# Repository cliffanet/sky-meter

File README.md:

# Высотомер Sky-Meter

Инструмент для парашютиста - простой высотомер на базе барометра.

***
## Что умеет

* измерять высоту;
* определять начала подъёма и начало прыжка;
* писать в логбук историю прыжков: время взлёта, высота отделения, высота раскрытия;

***
## Внутри

***
## Документация

* [Исходники](doc/code.md) - где, что лежит, права на использование, помощь при компиляции.
* [Где скачать](doc/download.md)

***
## Известные проблемы

- повышенное энергопотребление в спящем режиме (850 мкА)

    В первой аппаратной версии применялся чип stm32f473 и энергопотребление всего устройства
    на его основе удалось снизить до 125 мкА, а в выключенном - до 85-90 мкА. И это
    при заявленных в документации 56 мкА (что-то дополнительно подребляет и сама плата).

    А вот на чипе stm32f411 при заявленных в документации 10 мкА получить потребление ниже
    60 мкА так и не удалось - но это на пустой прошивке. На боевой же прошивке почему-то
    не отключаются какие-то узлы, и потребление ~850 мкА. С этим ещё предстоит разобраться.

- нестабильная работа с SD-картой

    Проблема возникает из-за слабого питания, подаваемого на карту. В целях экономии заряда
    батареи питание на SD-карту выведено напрямую с пина микроконтроллера. Применение дополнительного
    транзистора в режиме ключа вызывает проблемы из-за низкого потребляемого тока карты (несколько мА).
    При инициализации карты ток возрастает и питание проседает, из-за чего карта сбрасывается.

    Некоторые карты всё же работают, но таких мало.

    На stm32g4xx работа карт от пина была гораздо стабильнее. Но всё же, на некоторых картах тоже
    были сбои.

    В качестве оперативной меры можно перерезать дорожку, ведущую к пину МК и соединить питание карты
    напрямую на 3.3v. Однако потребление в спящем режиме вместе с SD-картой возрастает до 3 мА.

- отсутствие приложения для импорта логбука

    Разработка отложена на неопределённый срок.

***

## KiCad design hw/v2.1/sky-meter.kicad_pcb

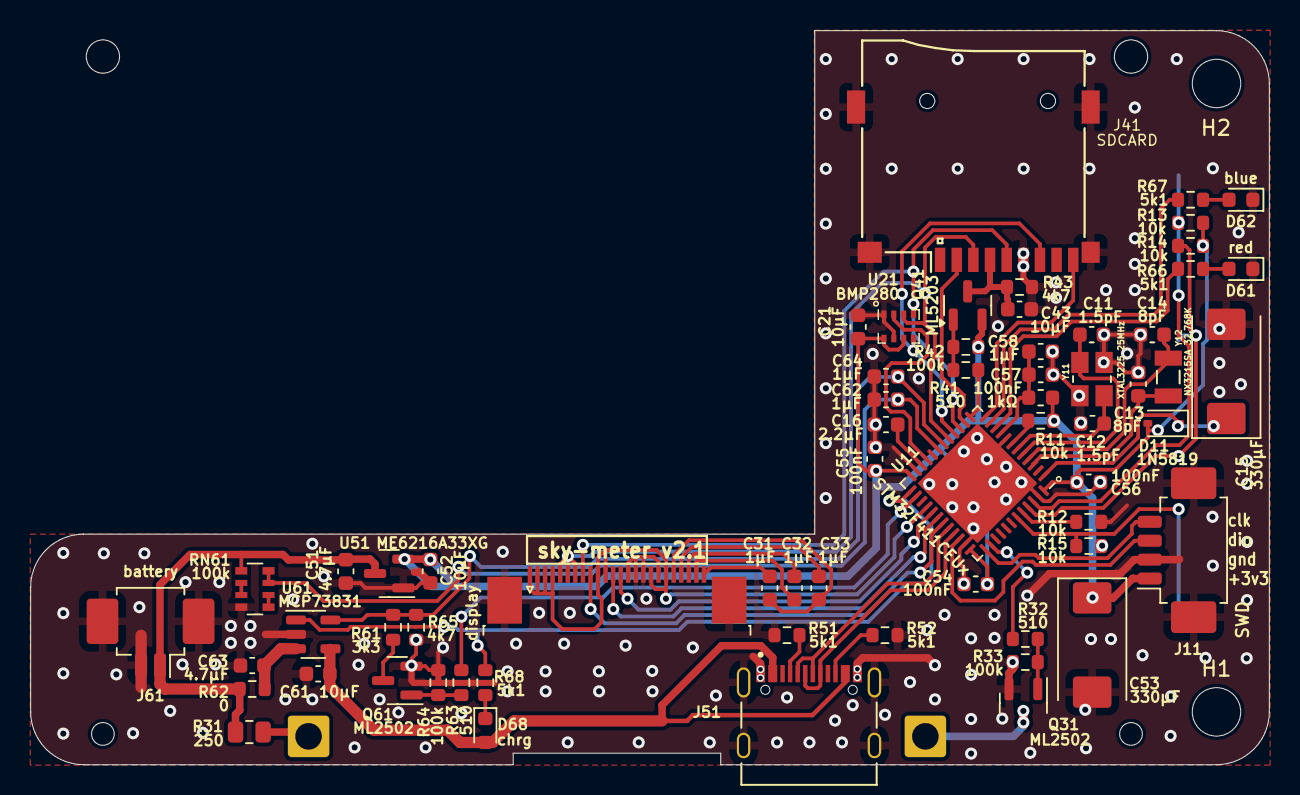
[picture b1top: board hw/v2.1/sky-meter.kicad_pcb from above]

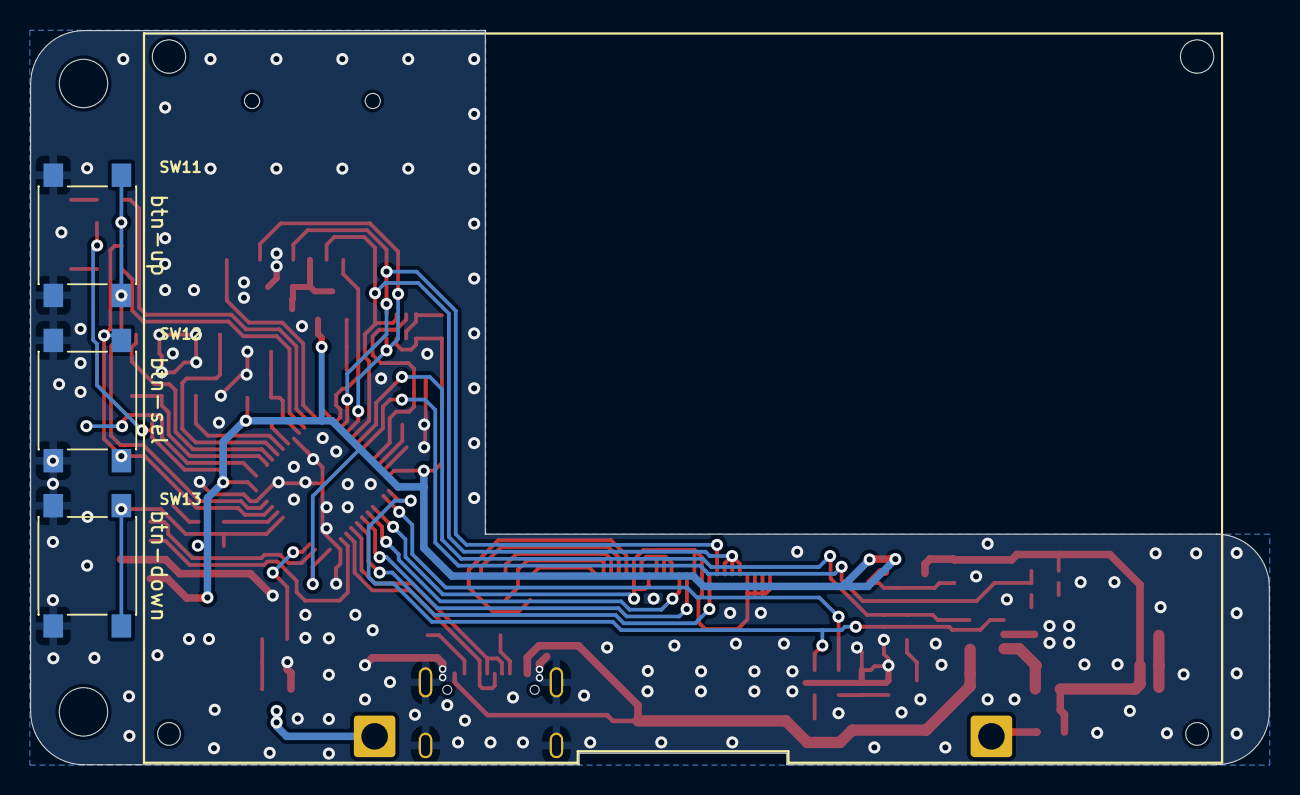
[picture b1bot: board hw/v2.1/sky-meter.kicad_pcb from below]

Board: 2 copper layers, 81.9 x 48.5 mm, 70 parts (3 on the bottom side), 58 nets.

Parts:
C11, C12: 1.5pF; C_0603_1608Metric
C13, C14: 8pF; C_0603_1608Metric
C15, C53: 330μF; CP_EIA-7343-20_Kemet-V
C16: 2.2μF; C_0603_1608Metric
C21, C43, C52, C61: 10μF; C_0603_1608Metric
C31, C32, C33, C58, C62, C64: 1μF; C_0603_1608Metric
C51, C63: 4.7μF; C_0603_1608Metric
C54, C55, C56, C57: 100nF; C_0603_1608Metric
D11: 1N5819; D_SOD-323
D61: red; LED_0603_1608Metric
D62: blue; LED_0603_1608Metric
D68: chrg; LED_0603_1608Metric
FB51: 1kΩ; L_0603_1608Metric
H1, H2: MountingHole; MountingHole_3.2mm_M3
J11: SWD; Molex_PicoBlade_53261-0471_1x04-1MP_P1.25mm_Horizontal
J31: display; TE_2-1734839-4_1x24-1MP_P0.5mm_Horizontal
J32: display-128x64
J41: SDCARD; Conn_uSDcard
J51: TYPE-C-31-M-12; HRO_TYPE-C-31-M-12
J61: battery; Molex_PicoBlade_53261-0271_1x02-1MP_P1.25mm_Horizontal
Q31, Q61: ML2502; SOT-23
Q41: ML5203; SOT-23
R11, R12, R13, R14, R15: 10k; R_0603_1608Metric
R31: 250; R_0805_2012Metric
R32, R41, R63: 510; R_0603_1608Metric
R33, R42, R64: 100k; R_0603_1608Metric
R43, R65: 4k7; R_0603_1608Metric
R51, R52, R66, R67, R68: 5k1; R_0603_1608Metric
R61: 3k3; R_0603_1608Metric
R62: 0; R_0603_1608Metric
RN61: 100k; R_Array_Convex_4x0603
SW11: btn-up; SW_Push_1P1T_NO_6x6mm_H9.5mm
SW12: btn-sel; SW_Push_1P1T_NO_6x6mm_H9.5mm
SW13: btn-down; SW_Push_1P1T_NO_6x6mm_H9.5mm
U11: STM32F411CEUx; QFN-48-1EP_7x7mm_P0.5mm_EP5.6x5.6mm
U21: BMP280; Bosch_LGA-8_2x2.5mm_P0.65mm_ClockwisePinNumbering
U51: ME6216A33XG; SOT-23
U61: MCP73831; SOT-23-5
Y11: XTAL3225 25MHz; XTAL_TSX-3225_16.0000MF18X-AC3
Y12: NX3215SA 32.768K; XTAL_NX3215SA-32.768K-STD-MUA-14

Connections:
+3.3VA: C57.2, C58.2, FB51.2, U11.9 (VDDA)
+3V3: C21.1, C52.2, C53.1, C54.1, C55.1, C56.1, D11.2 (A), FB51.1, J11.1, Q41.2 (S), R11.1, R13.1, R14.1, R15.1, R42.2, U11.24 (VDD), U11.36 (VDD), U11.48 (VDD), U21.6 (VDDIO), U21.8 (VDD), U51.2 (VO)
+BATT: C51.1, J61.1, R31.2, R62.2, RN61.1 (R1.1), U51.3 (VI)
/btn-dn: R15.2, SW13.2 (B), U11.43 (PB7)
/btn-sel: R14.2, SW12.2 (B), U11.45 (PB8)
/btn-up: R13.2, SW11.2 (B), U11.46 (PB9)
/d-cs: J31.13, U11.29 (PA8)
/d-en: J31.1, J31.2, J31.3, J31.4, J31.10, J31.11, J31.17, J31.19, U11.28 (PB15)
/d-rs-dc: J31.12, U11.30 (PA9)
/d-rst: J31.9, U11.31 (PA10)
/led-b: R67.2, U11.11 (PA1)
/led-r: R66.2, U11.10 (PA0)
/sdcard-cd: J41.9 (CD), U11.12 (PA2)
/sdcard-cs: J41.2 (CS/DAT3), U11.14 (PA4)
/sdcard-en: R41.2, U11.13 (PA3)
/spi-clk: J31.8, J41.5 (CLK), U11.15 (PA5), U21.4 (SCK)
/spi-miso: J41.7 (DO/DAT0), U11.16 (PA6), U21.5 (SDO)
/spi-mosi: J31.5, J31.6, J31.7, J41.3 (DI/CMD), U11.17 (PA7), U21.3 (SDI)
/swclk: J11.4, U11.37 (PA14)
/swdio: J11.3, U11.34 (PA13)
/usb-d+: J51.A6 (DP1), J51.B6 (DP2), U11.33 (PA12)
/usb-d-: J51.A7 (DN1), J51.B7 (DN2), U11.32 (PA11)
GND: C11.1, C12.1, C13.1, C14.1, C15.2, C16.2, C21.2, C43.1, C51.2, C52.1, C53.2, C54.2, C55.2, C56.2, C57.1, C58.1, C61.2, C62.2, C63.2, C64.2, D61.1 (K), D62.1 (K), J11.2, J11.MP (MountPin), J31.14, J31.15, J31.16, J31.18, J31.MP (MountPin), J41.6 (GND), J51.A1_B12 (GND), J51.B1_A12 (GND), J51.S1 (SHIELD), J51.S2 (SHIELD), J51.S3 (SHIELD), J51.S4 (SHIELD), J61.2, J61.MP (MountPin), Q31.2 (S), Q61.2 (S), R12.2, R33.2, R43.2, R51.1, R52.2, R64.2, R65.2, RN61.4 (R4.1), SW11.1 (A), SW12.1 (A), SW13.1 (A), U11.8 (VSSA), U11.23 (VSS), U11.35 (VSS), U11.47 (VSS), U11.49 (VSS), U21.1 (GND), U21.7 (GND), U51.1 (GND), U61.2 (VSS), Y11.2, Y11.4
unnamed: C15.1, D11.1 (K), U11.1 (VBAT)
unnamed: D61.2 (A), R66.1
unnamed: D62.2 (A), R67.1
unnamed: D68.1 (K), R68.1
unnamed: C31.1, C33.1, J31.20
unnamed: C33.2, J31.21
unnamed: C32.2, J31.22
unnamed: C32.1, J31.23
unnamed: C31.2, J31.24
unnamed: J32.1, R31.1
unnamed: J32.2, Q31.3 (D)
unnamed: C43.2, J41.4 (Vdd), Q41.3 (D), R43.1
unnamed: J51.A5 (CC1), R51.2
unnamed: J51.B5 (CC2), R52.1
unnamed: Q31.1 (G), R32.1, R33.1
unnamed: Q41.1 (G), R41.1, R42.1
unnamed: Q61.3 (D), R61.2
unnamed: Q61.1 (G), R63.1, R64.1
unnamed: RN61.2 (R2.1), RN61.3 (R3.1)
unnamed: RN61.5 (R4.2), RN61.6 (R3.2)
unnamed: R12.1, U11.44 (BOOT0)
unnamed: R11.2, U11.7 (NRST)
unnamed: C13.2, U11.3 (PC14), Y12.2
unnamed: C14.2, U11.4 (PC15), Y12.1
unnamed: C11.2, U11.5 (PH0), Y11.1
unnamed: C12.2, U11.6 (PH1), Y11.3
unnamed: C16.1, U11.22 (VCAP1)
unnamed: C63.1, R62.1, U61.3 (VBAT)
batt-info: C62.1, RN61.7 (R2.2), RN61.8 (R1.2), U11.19 (PB1)
bmp280-cs: U11.21 (PB10), U21.2 (CSB)
chg-cur: C64.1, R61.1, R65.1, U11.18 (PB0), U61.5 (PROG)
chg-hi: R63.2, U11.26 (PB13)
chg-ind: R68.2, U11.25 (PB12), U61.1 (STAT)
d-led: R32.2, U11.38 (PA15)
usb-5v: C61.1, D68.2 (A), J51.A4_B9 (VBUS), J51.B4_A9 (VBUS), U61.4 (VDD)

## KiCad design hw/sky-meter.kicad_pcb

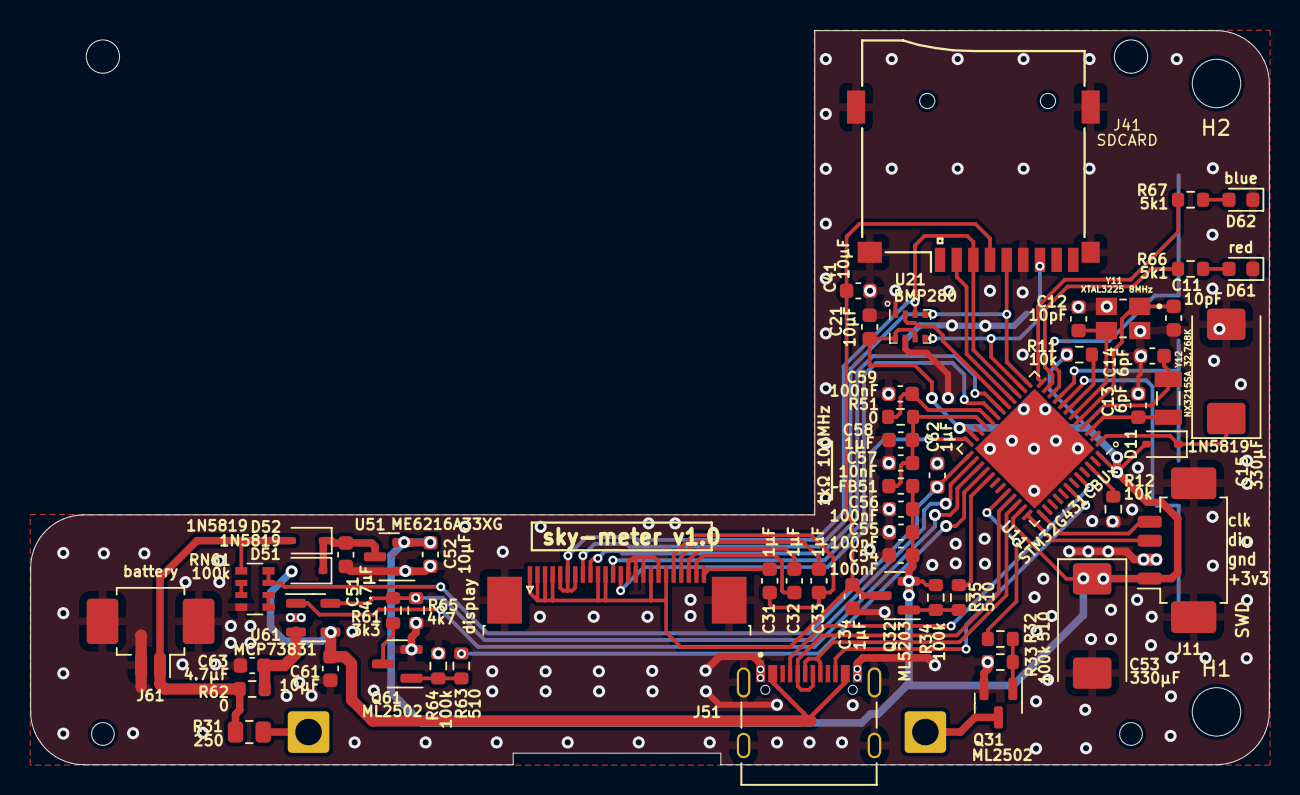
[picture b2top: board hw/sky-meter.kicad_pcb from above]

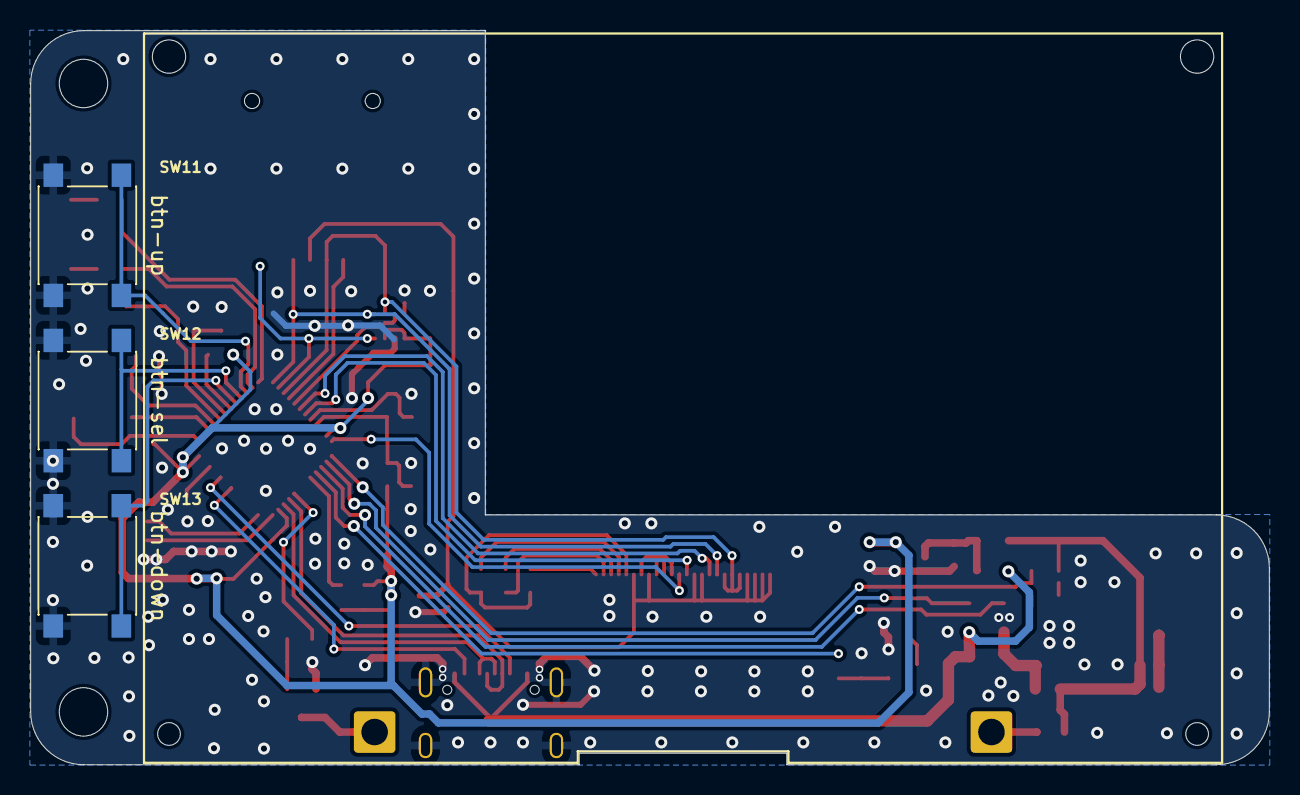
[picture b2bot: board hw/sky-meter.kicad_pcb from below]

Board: 2 copper layers, 81.9 x 48.5 mm, 65 parts (3 on the bottom side), 56 nets.

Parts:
C11, C12: 10pF; C_0603_1608Metric
C13, C14: 6pF; C_0603_1608Metric
C15, C53: 330μF; CP_EIA-7343-20_Kemet-V
C21, C41, C52, C61: 10μF; C_0603_1608Metric
C31, C32, C33, C34, C58, C62: 1μF; C_0603_1608Metric
C51, C63: 4.7μF; C_0603_1608Metric
C54, C55, C56, C59: 100nF; C_0603_1608Metric
C57: 10nF; C_0603_1608Metric
D11, D51, D52: 1N5819; D_SOD-323
D61: red; LED_0603_1608Metric
D62: blue; LED_0603_1608Metric
FB51: 1kΩ 100MHz; L_0603_1608Metric
H1, H2: MountingHole; MountingHole_3.2mm_M3
J11: SWD; Molex_PicoBlade_53261-0471_1x04-1MP_P1.25mm_Horizontal
J31: display; TE_2-1734839-4_1x24-1MP_P0.5mm_Horizontal
J32: display-256x192
J41: SDCARD; Conn_uSDcard
J51: TYPE-C-31-M-12; HRO_TYPE-C-31-M-12
J61: battery; Molex_PicoBlade_53261-0271_1x02-1MP_P1.25mm_Horizontal
Q31, Q61: ML2502; SOT-23
Q32: ML5203; SOT-23
R11, R12: 10k; R_0603_1608Metric
R31: 250; R_0805_2012Metric
R32, R35, R63: 510; R_0603_1608Metric
R33, R34, R64: 100k; R_0603_1608Metric
R51, R62: 0; R_0603_1608Metric
R61: 3k3; R_0603_1608Metric
R65: 4k7; R_0603_1608Metric
R66, R67: 5k1; R_0603_1608Metric
RN61: 100k; R_Array_Convex_4x0603
SW11: btn-up; SW_Push_1P1T_NO_6x6mm_H9.5mm
SW12: btn-sel; SW_Push_1P1T_NO_6x6mm_H9.5mm
SW13: btn-down; SW_Push_1P1T_NO_6x6mm_H9.5mm
U11: STM32G431CBUx; QFN-48-1EP_7x7mm_P0.5mm_EP5.6x5.6mm
U21: BMP280; Bosch_LGA-8_2x2.5mm_P0.65mm_ClockwisePinNumbering
U51: ME6216A33XG; SOT-23
U61: MCP73831; SOT-23-5
Y11: XTAL3225 8MHz; XTAL_TSX-3225_16.0000MF18X-AC3
Y12: NX3215SA 32.768K; XTAL_NX3215SA-32.768K-STD-MUA-14

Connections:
+3.3VA: C57.1, C58.1, FB51.2, R51.1, U11.21 (VDDA)
+3V3: C21.1, C52.2, C53.1, C54.1, C55.1, C56.1, D11.2 (A), FB51.1, J11.1, Q32.2 (S), R11.1, R34.1, U11.23 (VDD), U11.35 (VDD), U11.48 (VDD), U21.6 (VDDIO), U21.8 (VDD), U51.2 (VO)
+BATT: D52.2 (A), J61.1, R31.2, R62.2, RN61.1 (R1.1)
/btn-dn: SW13.2 (B), U11.8 (PA0)
/btn-sel: SW12.2 (B), U11.9 (PA1)
/btn-up: SW11.2 (B), U11.10 (PA2)
/d-cs: J31.13, U11.24 (PB11)
/d-rs-dc: J31.12, U11.19 (PB2)
/d-rst: J31.9, U11.18 (PB1)
/led-b: R67.2, U11.12 (PA4)
/led-r: R66.2, U11.11 (PA3)
/spi-clk: J31.8, J41.5 (CLK), U11.13 (PA5), U21.4 (SCK)
/spi-miso: J41.7 (DO/DAT0), U11.14 (PA6), U21.5 (SDO)
/spi-mosi: J31.5, J31.6, J31.7, J41.3 (DI/CMD), U11.15 (PA7), U21.3 (SDI)
/swclk: J11.4, U11.37 (PA14)
/swdio: J11.3, U11.36 (PA13)
/usb-cc1: J51.A5 (CC1), U11.44 (PB6)
/usb-cc2: J51.B5 (CC2), U11.42 (PB4)
/usb-d+: J51.A6 (DP1), J51.B6 (DP2), U11.34 (PA12)
/usb-d-: J51.A7 (DN1), J51.B7 (DN2), U11.33 (PA11)
GND: C11.1, C12.1, C13.1, C14.1, C15.2, C21.2, C34.2, C41.2, C51.2, C52.1, C53.2, C54.2, C55.2, C56.2, C57.2, C58.2, C59.2, C61.2, C62.2, C63.2, D61.1 (K), D62.1 (K), J11.2, J11.MP (MountPin), J31.14, J31.15, J31.16, J31.18, J31.MP (MountPin), J41.6 (GND), J51.A1_B12 (GND), J51.B1_A12 (GND), J51.S1 (SHIELD), J51.S2 (SHIELD), J51.S3 (SHIELD), J51.S4 (SHIELD), J61.2, J61.MP (MountPin), Q31.2 (S), Q61.2 (S), R12.1, R33.2, R64.2, R65.2, RN61.4 (R4.1), SW11.1 (A), SW12.1 (A), SW13.1 (A), U11.49 (VSS), U21.1 (GND), U21.7 (GND), U51.1 (GND), U61.2 (VSS), Y11.2, Y11.4
unnamed: C15.1, D11.1 (K), U11.1 (VBAT)
unnamed: C51.1, D51.1 (K), D52.1 (K), U51.3 (VI)
unnamed: D61.2 (A), R66.1
unnamed: D62.2 (A), R67.1
unnamed: C31.1, C33.1, J31.20
unnamed: C33.2, J31.21
unnamed: C32.2, J31.22
unnamed: C32.1, J31.23
unnamed: C31.2, J31.24
unnamed: J32.1, R31.1
unnamed: J32.2, Q31.3 (D)
unnamed: Q31.1 (G), R32.1, R33.1
unnamed: Q32.1 (G), R34.2, R35.2
unnamed: Q61.3 (D), R61.2
unnamed: Q61.1 (G), R63.1, R64.1
unnamed: RN61.2 (R2.1), RN61.3 (R3.1)
unnamed: RN61.5 (R4.2), RN61.6 (R3.2)
unnamed: R12.2, U11.46 (PB8)
unnamed: C13.2, U11.3 (PC14), Y12.2
unnamed: C14.2, U11.4 (PC15), Y12.1
unnamed: C11.2, U11.5 (PF0), Y11.1
unnamed: C12.2, U11.6 (PF1), Y11.3
unnamed: R11.2, U11.7 (PG10)
unnamed: C63.1, R62.1, U61.3 (VBAT)
V-ref: C59.1, R51.2, U11.20 (VREF+)
batt-info: C62.1, RN61.7 (R2.2), RN61.8 (R1.2), U11.25 (PB12)
bmp280-cs: U11.17 (PB0), U21.2 (CSB)
chg-cur: R61.1, R65.1, U11.26 (PB13), U61.5 (PROG)
chg-hi: R63.2, U11.28 (PB15)
chg-ind: U11.27 (PB14), U61.1 (STAT)
d-led: R32.2, U11.32 (PA10)
hwen: R35.1, U11.29 (PC6)
hwpwr: C34.1, C41.1, J31.1, J31.2, J31.3, J31.4, J31.10, J31.11, J31.17, J31.19, J41.4 (Vdd), Q32.3 (D)
sdcard-cs: J41.2 (CS/DAT3), U11.16 (PC4)
usb-5v: C61.1, D51.2 (A), J51.A4_B9 (VBUS), J51.B4_A9 (VBUS), U61.4 (VDD)

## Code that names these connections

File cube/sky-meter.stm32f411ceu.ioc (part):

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Mcu.Name=STM32F411C(C-E)Ux
Mcu.Package=UFQFPN48
Mcu.UserName=STM32F411CEUx
PA0-WKUP.GPIOParameters=GPIO_Label
PA0-WKUP.GPIO_Label=led red
PA0-WKUP.Signal=GPIO_Output
PA1.GPIOParameters=GPIO_Label
PA1.GPIO_Label=led blue
PA1.Signal=GPIO_Output
PA10.GPIOParameters=GPIO_Label
PA10.GPIO_Label=display rst
PA10.Signal=GPIO_Output
PA11.Mode=Device_Only
PA11.Signal=USB_OTG_FS_DM
PA12.Mode=Device_Only
PA12.Signal=USB_OTG_FS_DP
PA15.GPIOParameters=GPIO_Label
PA15.GPIO_Label=display light
PA15.Signal=GPIO_Output
PA2.GPIOParameters=GPIO_PuPd,GPIO_Label
PA2.GPIO_Label=sdcard cd
PA2.GPIO_PuPd=GPIO_PULLUP
PA2.Signal=GPIO_Input
PA3.GPIOParameters=PinState,GPIO_Label
PA3.GPIO_Label=sdcard en
PA3.PinState=GPIO_PIN_SET
PA3.Signal=GPIO_Output
PA4.GPIOParameters=PinState,GPIO_Label
PA4.GPIO_Label=sdcard cs
PA4.PinState=GPIO_PIN_SET
PA4.Signal=GPIO_Output
PA5.Mode=Full_Duplex_Master
PA5.Signal=SPI1_SCK
PA6.Mode=Full_Duplex_Master
PA6.Signal=SPI1_MISO
PA7.Mode=Full_Duplex_Master
PA7.Signal=SPI1_MOSI
PA8.GPIOParameters=PinState,GPIO_Label
PA8.GPIO_Label=display cs
PA8.PinState=GPIO_PIN_SET
PA8.Signal=GPIO_Output
PA9.GPIOParameters=GPIO_Label
PA9.GPIO_Label=display rs-dc
PA9.Signal=GPIO_Output
PB0.GPIOParameters=GPIO_Label
PB0.GPIO_Label=chg cur
PB0.Signal=GPIO_Analog
PB1.GPIOParameters=GPIO_Label
PB1.GPIO_Label=batt info
PB1.Signal=ADCx_IN9
PB10.GPIOParameters=PinState,GPIO_Label
PB10.GPIO_Label=bmp280 cs
PB10.PinState=GPIO_PIN_SET
PB10.Signal=GPIO_Output
PB12.GPIOParameters=GPIO_PuPd,GPIO_Label
PB12.GPIO_Label=chg ind
PB12.GPIO_PuPd=GPIO_PULLUP
PB12.Signal=GPIO_Input
PB13.GPIOParameters=GPIO_Label
PB13.GPIO_Label=chg hi
PB13.Signal=GPIO_Output
PB15.GPIOParameters=PinState,GPIO_Label
PB15.GPIO_Label=display en
PB15.PinState=GPIO_PIN_SET
PB15.Signal=GPIO_Output
PB7.GPIOParameters=GPIO_Label,GPIO_ModeDefaultEXTI
PB7.GPIO_Label=btn dn
PB7.GPIO_ModeDefaultEXTI=GPIO_MODE_IT_RISING_FALLING
PB7.Signal=GPXTI7
PB8.GPIOParameters=GPIO_Label,GPIO_ModeDefaultEXTI
PB8.GPIO_Label=btn sel
PB8.GPIO_ModeDefaultEXTI=GPIO_MODE_IT_RISING_FALLING
PB8.Signal=GPXTI8
PB9.GPIOParameters=GPIO_Label,GPIO_ModeDefaultEXTI
PB9.GPIO_Label=btn up
PB9.GPIO_ModeDefaultEXTI=GPIO_MODE_IT_RISING_FALLING
PB9.Signal=GPXTI9
PC14-OSC32_IN.Mode=LSE-External-Oscillator
PC14-OSC32_IN.Signal=RCC_OSC32_IN
PC15-OSC32_OUT.Mode=LSE-External-Oscillator
PC15-OSC32_OUT.Signal=RCC_OSC32_OUT
PH0\ -\ OSC_IN.Mode=HSE-External-Oscillator
PH0\ -\ OSC_IN.Signal=RCC_OSC_IN
PH1\ -\ OSC_OUT.Mode=HSE-External-Oscillator
PH1\ -\ OSC_OUT.Signal=RCC_OSC_OUT
RCC.HSE_VALUE=25000000
RCC.SYSCLKFreq_VALUE=96000000
RCC.SYSCLKSource=RCC_SYSCLKSOURCE_PLLCLK
board=custom

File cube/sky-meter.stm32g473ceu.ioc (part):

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Mcu.Name=STM32G473C(B-C-E)Ux
Mcu.Package=UFQFPN48
Mcu.UserName=STM32G473CEUx
PA0.GPIOParameters=GPIO_PuPd,GPIO_Label,GPIO_ModeDefaultEXTI
PA0.GPIO_Label=btn dn
PA0.GPIO_ModeDefaultEXTI=GPIO_MODE_IT_RISING_FALLING
PA0.GPIO_PuPd=GPIO_PULLUP
PA0.Signal=GPXTI0
PA1.GPIOParameters=GPIO_PuPd,GPIO_Label,GPIO_ModeDefaultEXTI
PA1.GPIO_Label=btn sel
PA1.GPIO_ModeDefaultEXTI=GPIO_MODE_IT_RISING_FALLING
PA1.GPIO_PuPd=GPIO_PULLUP
PA1.Signal=GPXTI1
PA10.GPIOParameters=GPIO_Label
PA10.GPIO_Label=display light
PA10.Signal=GPIO_Output
PA11.Mode=Device
PA11.Signal=USB_DM
PA12.Mode=Device
PA12.Signal=USB_DP
PA2.GPIOParameters=GPIO_PuPd,GPIO_Label,GPIO_ModeDefaultEXTI
PA2.GPIO_Label=btn up
PA2.GPIO_ModeDefaultEXTI=GPIO_MODE_IT_RISING_FALLING
PA2.GPIO_PuPd=GPIO_PULLUP
PA2.Signal=GPXTI2
PA3.GPIOParameters=GPIO_Label
PA3.GPIO_Label=led red
PA3.Signal=GPIO_Output
PA4.GPIOParameters=GPIO_Label
PA4.GPIO_Label=led blue
PA4.Signal=GPIO_Output
PA5.Mode=Full_Duplex_Master
PA5.Signal=SPI1_SCK
PA6.Mode=Full_Duplex_Master
PA6.Signal=SPI1_MISO
PA7.Mode=Full_Duplex_Master
PA7.Signal=SPI1_MOSI
PB0.GPIOParameters=PinState,GPIO_Label
PB0.GPIO_Label=bmp280 cs
PB0.PinState=GPIO_PIN_SET
PB0.Signal=GPIO_Output
PB1.GPIOParameters=GPIO_Label
PB1.GPIO_Label=display rst
PB1.Signal=GPIO_Output
PB11.GPIOParameters=PinState,GPIO_Label
PB11.GPIO_Label=display cs
PB11.PinState=GPIO_PIN_SET
PB11.Signal=GPIO_Output
PB12.GPIOParameters=GPIO_Label
PB12.GPIO_Label=batt info
PB12.Mode=IN11-Single-Ended
PB12.Signal=ADC1_IN11
PB14.GPIOParameters=GPIO_PuPd,GPIO_Label
PB14.GPIO_Label=chg ind
PB14.GPIO_PuPd=GPIO_PULLUP
PB14.Signal=GPIO_Input
PB15.GPIOParameters=GPIO_Label
PB15.GPIO_Label=chg hi
PB15.Signal=GPIO_Output
PB2.GPIOParameters=GPIO_Label
PB2.GPIO_Label=display rs-dc
PB2.Signal=GPIO_Output
PB4.Signal=UCPD1_CC2
PB6.Signal=UCPD1_CC1
PC14-OSC32_IN.Mode=LSE-External-Oscillator
PC14-OSC32_IN.Signal=RCC_OSC32_IN
PC15-OSC32_OUT.Mode=LSE-External-Oscillator
PC15-OSC32_OUT.Signal=RCC_OSC32_OUT
PC4.GPIOParameters=PinState,GPIO_Label
PC4.GPIO_Label=sdcard cs
PC4.PinState=GPIO_PIN_SET
PC4.Signal=GPIO_Output
PC6.GPIOParameters=PinState,GPIO_Label
PC6.GPIO_Label=hwen
PC6.PinState=GPIO_PIN_SET
PC6.Signal=GPIO_Output
PF0-OSC_IN.Mode=HSE-External-Oscillator
PF0-OSC_IN.Signal=RCC_OSC_IN
PF1-OSC_OUT.Mode=HSE-External-Oscillator
PF1-OSC_OUT.Signal=RCC_OSC_OUT
RCC.HSE_VALUE=8000000
RCC.SYSCLKFreq_VALUE=170000000
RCC.SYSCLKSource=RCC_SYSCLKSOURCE_PLLCLK
board=custom

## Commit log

2024-09-30 hw - схема
2024-10-03 hm - доработана схема
2024-10-05 разведена плата, надо проверять
2024-10-08 плата - доработана и отправлена в заказ v1.0
2024-10-21 заготовка cubemx-проекта
2024-10-22 часы и логи
2024-10-22 воркер (облегчённый, без shared_ptr)
2024-10-23 дисплей - основной функционал (стал использовать воркер, но теперь нет view-класса, только присвоение функции-рисовальщика)
2024-10-24 заготовка под отрисовку главной страницы
2024-10-24 инит часов - установка даты/времени компиляции прошивки
2024-10-25 кнопки - процессинг
2024-10-26 заготовка под меню
2024-10-27 menustatic, menu timeout
2024-10-27 модальные окна меню - форма подтверждения
2024-10-28 конфиг с сохранением во внутренней flash, теперь надо делать правки в меню и тестировать сохранение конфига
2024-10-29 меню - пункты изменения основного конфига
2024-10-31 конфиг - сохранение во flash
2024-11-02 bmp280
2024-11-02 jmp - лог высоты
2024-11-03 меню - много разных функций
2024-11-04 модуль power - заготовка под энергосбережение... но надо сначала переосмыслить работу устр-ва через таймеры
2024-11-06 основной цикл - с применением rtc таймера, убираем воркер - jmp
2024-11-07 убираем воркер - дисплей, меню
2024-11-08 убираем воркер - кнопки
2024-11-08 управление энергосбережением (требуется отладка)
2024-11-09 управление энергосбережением - поправлены баги
2024-11-09 работа часов без сброса при отсутствии питания
2024-11-10 небольшие доработки по пинам - hwen, led
2024-11-10 толщина платы - для корректной модели для внутрянки корпуса
2024-11-12 обработка батареи - требуется тестирование и отладка
2024-11-13 доработки по индикации батареи
2024-11-15 отключатели меню и графика прыжка
2024-11-16 корпус
2024-11-16 рефакторинг записи во внутреннюю флеш
2024-11-16 логбук - запись
2024-11-17 логбук - отображение в меню
2024-11-17 отображение фатальных ошибок системы на красном светодиоде
2024-11-23 доработки по энергопотреблению и режимам сон/выкл
2024-11-23 баги и доработки длительностей этапов прыжка в логбуке
2024-11-23 реорганизация под разные контроллеры
2024-11-23 реорганизация под разные контроллеры - g473
2024-11-23 фатальные ошибки перенесены в свой код
2024-11-24 реорганизация под разные контроллеры - доработки по g431
2024-11-24 доработки по спящему режиму и выходу в начале подъёма
2024-11-24 тестирование аппаратуры - вывод серийного номера чипа
2024-11-24 добавлены в конфиг пины USB-CC1/2
2024-12-01 поправлены параметры выхода из сна в начале подъёма
2024-12-07 доработки по питанию
2024-12-07 меню без автоматического закрытия
2024-12-07 доработки по отображению заряда батареи
2024-12-21 доработки по таймауту меню
2024-12-21 более быстрое (при удержании) изменение кол-ва прыжков в настройках
2024-12-21 логбук - переключение между прыжками внутри подробного инфо
2024-12-22 логбук - доработки
2024-12-23 доработки по внутренней флеш
2024-12-29 запись логбука и трассировки прыжка на sd-карту
2024-12-29 тестирование аппаратуры - sd карта
2024-12-30 рефакторинг altcalc - буфер высот вынесен в отдельный класс
2024-12-30 sd карта - несущественные доработки (пока ни на что не влияющие)
2025-01-06 доработки файлов на sd-карте
2025-01-06 доработки по энергосбережению
2025-01-06 приложение - заготовка
2025-01-07 приложение - загрузка и отрисовка графика из файла
2025-01-08 приложение - возможность двигать график пальцами
2025-01-08 приложение - масштабирование графика
2025-01-11 плата v2 - заменён проц на f4, доработки и баги с прошлой версии
2025-02-14 перемещаем код в cube - пока только корневые файлы
2025-02-14 перемещаем код в cube - Makefile
2025-02-14 перемещаем код в cube - source
2025-02-14 перенесён def.h, исправлены варнинги
2025-02-14 лог изменений hw/v2.0
2025-02-15 подготовка к f4
2025-02-15 переезд на stm32а411 - пины, временно отключен USB (с ним не стартует)
2025-02-15 доработки по bmp280 (на высокой частоте spi более 25МГц работает плохо)
2025-02-15 вернули usb (после перехода на f411 остались хвосты от g4 в Makefile)
2025-02-18 большая переработка взаимодействия с внутренней флеш, конфиг, логбук
2025-02-18 быг высотомера в спящем режиме
2025-02-20 попытка разобраться, почему перестала работать sd-карта (пока неуспешно)
2025-02-20 кажется, нашлась причина неподключения sd-карты
2025-02-22 доработки по энергопотреблению
2025-02-23 барометр - доработки по валидации получаемых данных
2025-02-25 документация (пока без картинок)
2025-02-27 документация - картинки
2025-02-27 барометр - доработки по возвращению из сна
2025-02-28 доработки Makefile
2025-02-28 документация - файлы на скачивание
2025-02-28 документация - доработки по сборке прошивки
2025-03-03 немного переделан модуль работы с sd-картой + выяснилось, что все проблемы с определением были из-за плохого питания
2025-03-04 поправлены прерывания кнопок
2025-03-04 баг уровня земли при пробуждении в подъёме
2025-03-04 документация - небольшая доработка основной страницы
2025-04-14 отключение питания - переделано через обращение напрямую к регистрам, полный сброс всех пинов, удалось уменьшить потребление до 120 мкА
2025-04-14 восстановлен индикатор заряда в спящем режиме
2025-04-15 работа с sd-картой через транзитор по питанию
2025-04-15 доработки по инициализации usb
2025-04-16 app - подключен и используется для отрисовки AltCalc
2025-04-17 app - вся математика в графиках переделана на матрицы
2025-04-17 app - курсор = отображение подробной инфы в определённой точке
2025-04-18 переработан модуль взаимодействия с bmp280 - код калькуляции взят максимально точно из datasheet
2025-04-20 модуль bmp280 - бага чтения калибровочных значений
2025-04-20 сохранение на sd-карту в фоне
2025-04-21 altcalc - подкручен профиль, убран strict-режим
2025-04-22 app - логбук - загрузка из папки (пока только сам логбук, без трассировок)
2025-04-22 app - логбук - переход в трассировку
2025-04-24 app - отрисовка графиков - переделана обратно на прямые безматричные вычисления - не смог добиться стабильного зума с привязкой к точке, если совмещать ещё с ручным перемещением.
2025-04-24 коммуникация с приложением - подключение и обмен командами
2025-04-25 app - получение с устройства логбука и трассировок
2025-04-26 app - доработки на случай неподгрузки jump(altcalc)
2025-04-26 app - доработки по сборке jump(altcalc) по windows
2025-04-27 app - иконки
2025-04-27 hw - добавлен индикатор зарядки и транзистор на питание sd-карты
2025-05-11 барометр - страница с графиком изменения давления за 10 часов
2025-05-25 app - баг парсинга даты/времени прыжка
2025-06-02 доработки по usb
2025-06-08 доработки по отправке bmp280 в сон
2025-06-08 box - версия с креплением на запястье
2025-06-08 skybook - синтаксические доработки
2025-06-08 skybook - цветовые обозначения в подсказке trace
2025-06-08 баг сохранения прыжка
2025-06-08 debug тестирование sd-карты
2025-06-08 fw version
2025-06-09 логбук - информация, есть ли трассировка к прыжку
2025-06-14 box - доработки краёв корпуса
2025-06-22 доработки по инициализации sd-карты сразу после подачи питания
2025-06-29 скидывание лог-буфера на sd-карту после прыжка
2025-08-21 коды критических ошибок на дисплей
